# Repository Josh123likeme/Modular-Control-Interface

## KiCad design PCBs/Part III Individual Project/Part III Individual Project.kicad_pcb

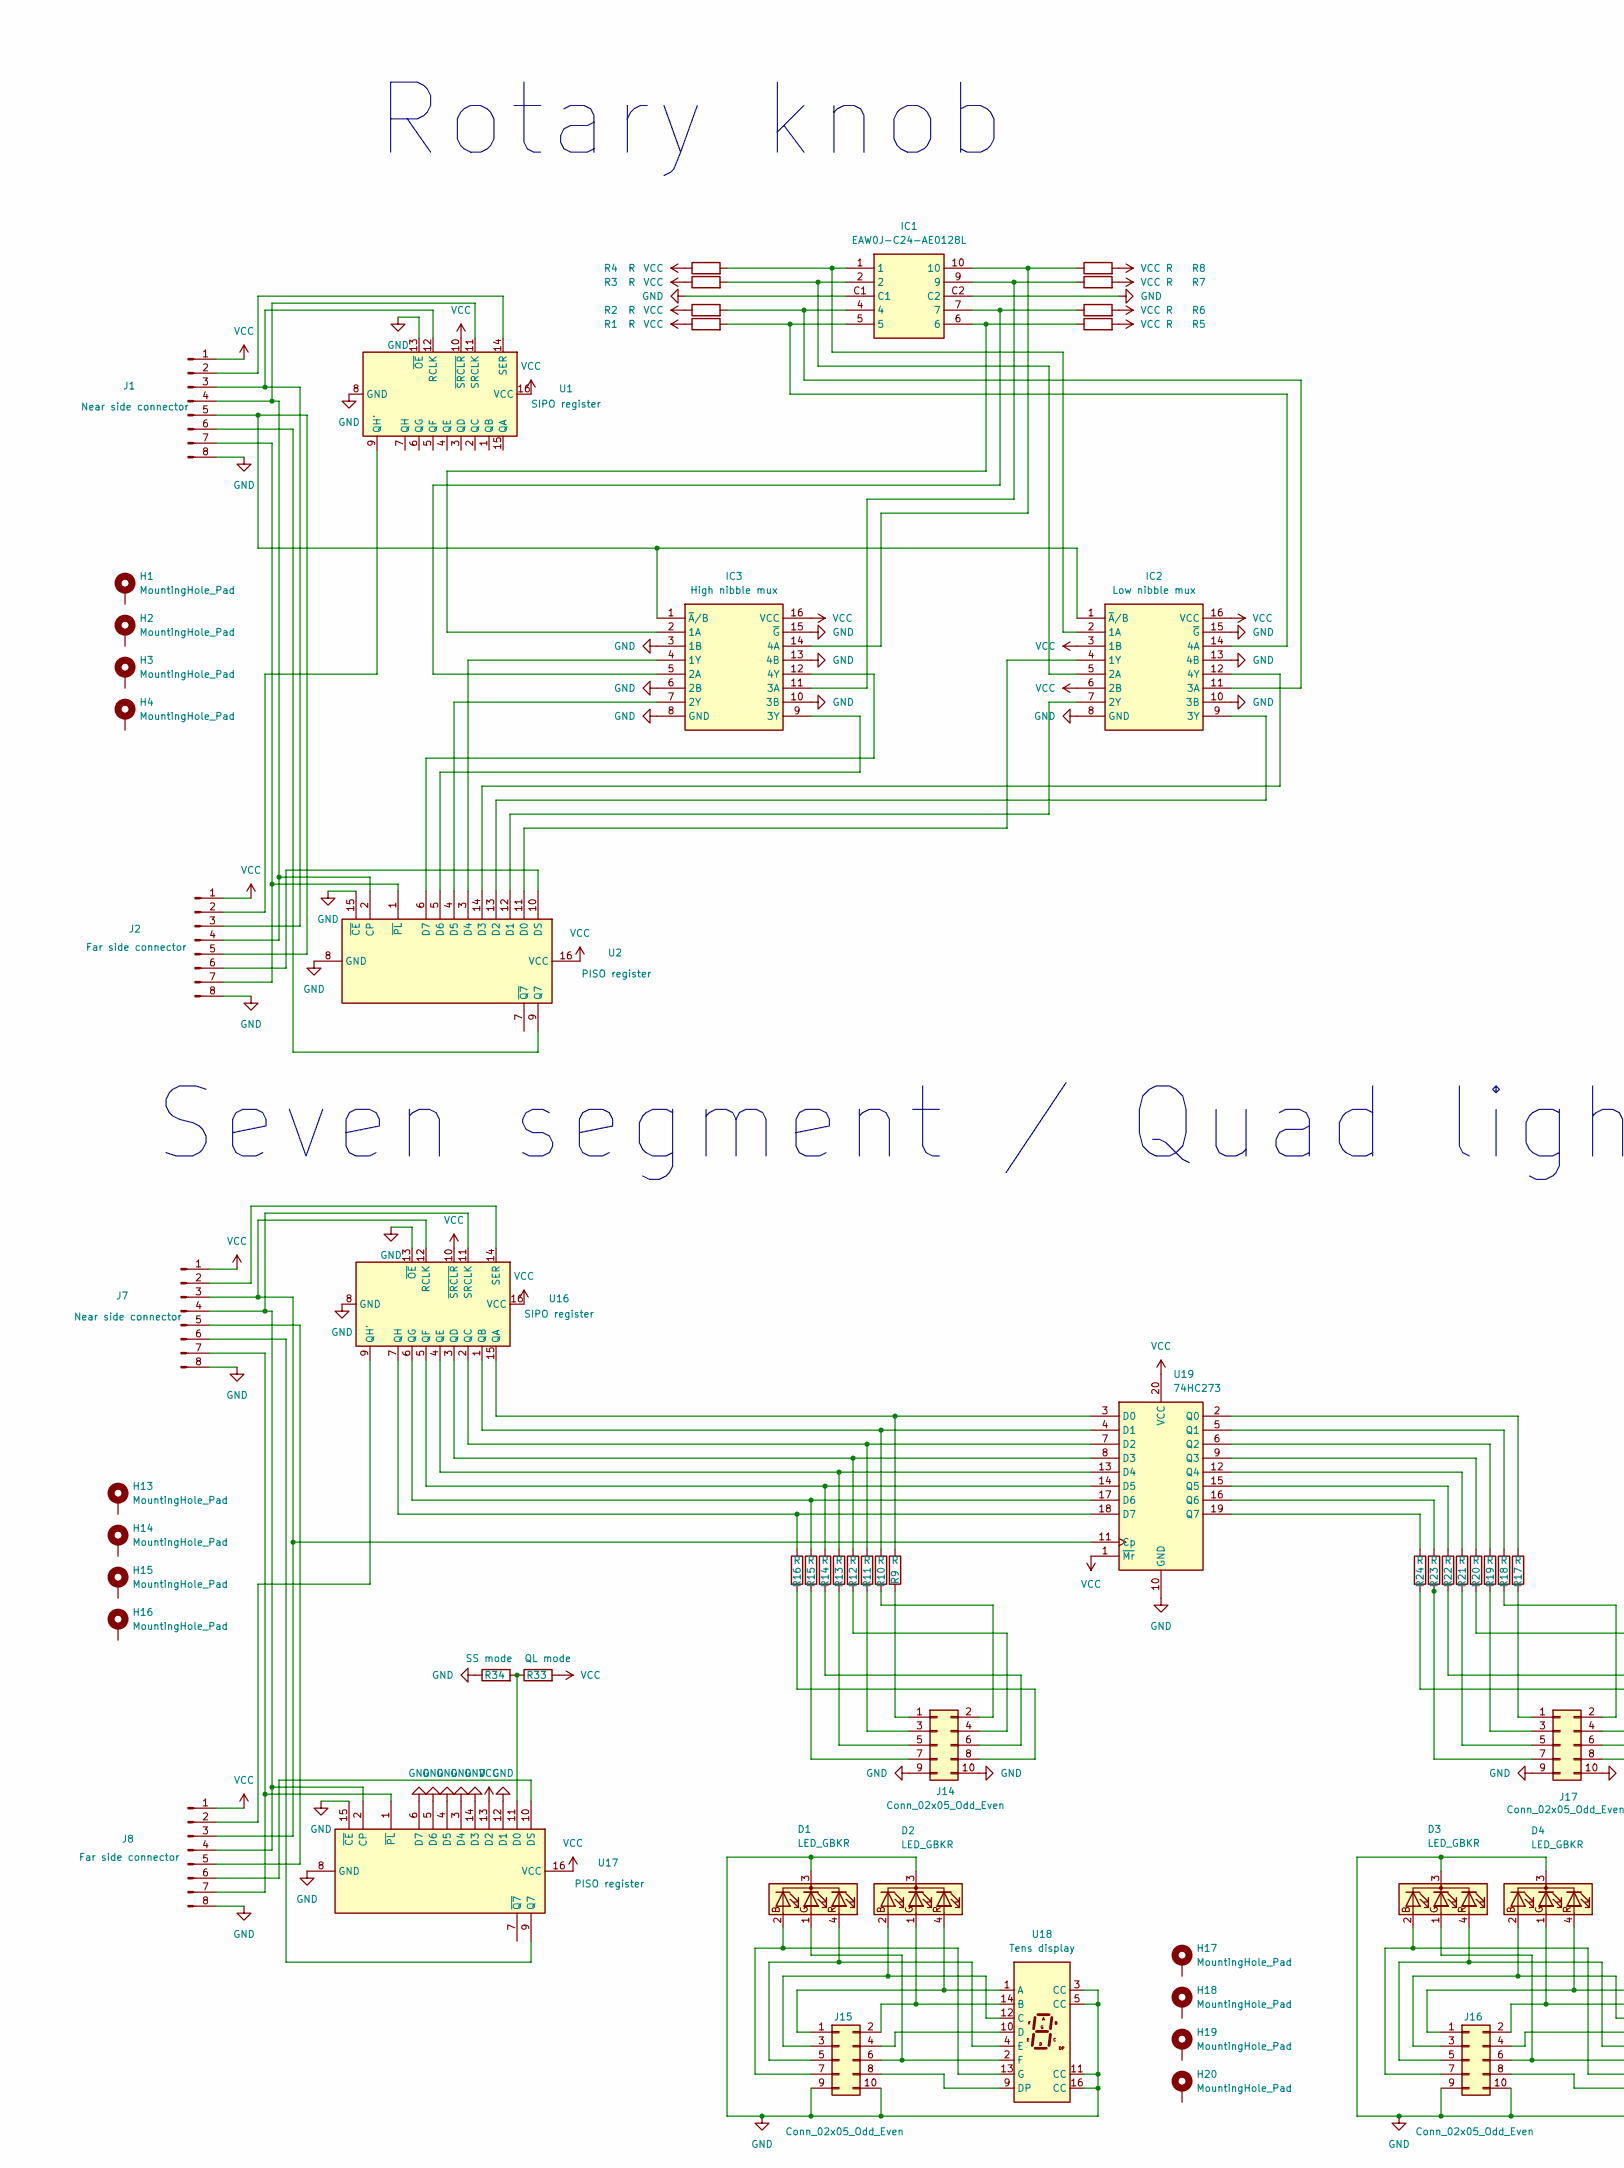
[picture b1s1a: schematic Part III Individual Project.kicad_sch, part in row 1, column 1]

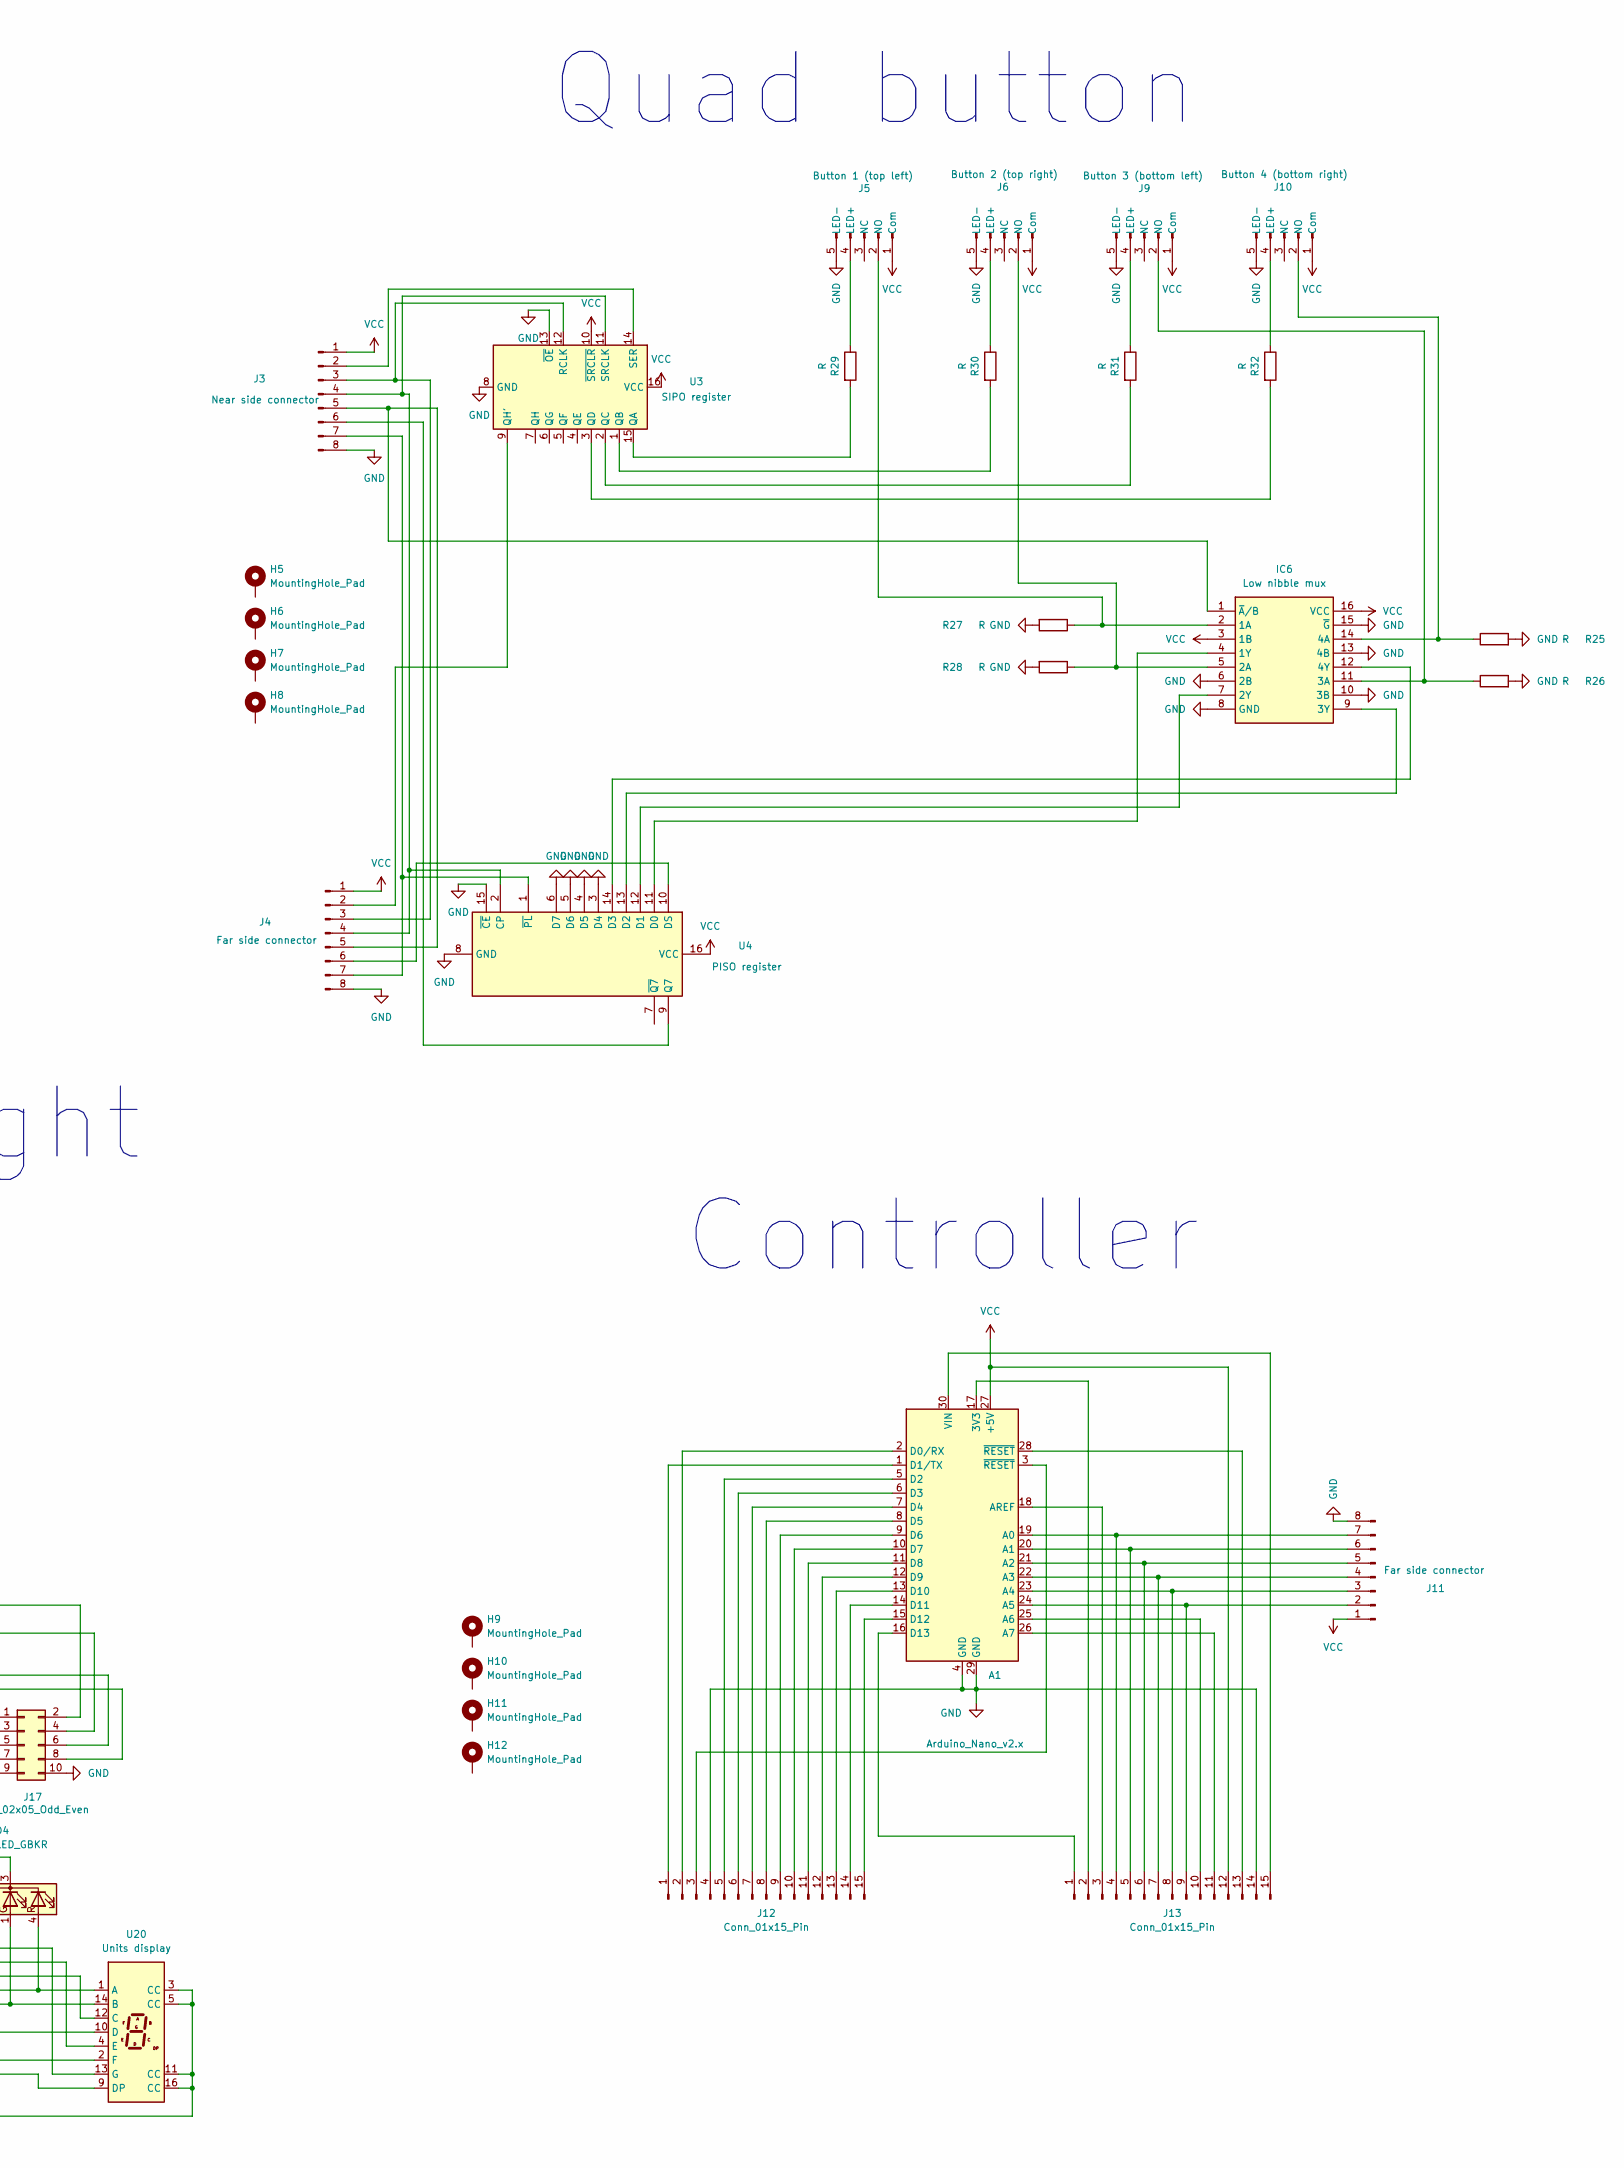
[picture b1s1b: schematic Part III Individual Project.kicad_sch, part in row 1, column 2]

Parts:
A1: Arduino_Nano_v2.x; Arduino Nano ATMEGA328P Headers Face Down
D1, D2, D3, D4: LED_GBKR; LED_D5.0mm-4_RGB_Wide_Pins
H1, H2, H3, H4, H5, H6, H7, H8, H9, H10, H11, H12, H13, H14, H15, H16, H17, H18, H19, H20: MountingHole_Pad; MountingHole_3.2mm_M3_Pad_Via
IC1: EAW0J-C24-AE0128L; EAW0JC24AE0128L; Mouser Part Number 652-EAW0J-C24-AEL
IC2, IC6: Low nibble mux; SOIC-16_3.9x9.9mm_P1.27mm; Mouser Part Number 595-SN74HC157DBR
IC3: High nibble mux; SOIC-16_3.9x9.9mm_P1.27mm; Mouser Part Number 595-SN74HC157DBR
J1, J3, J7: Near side connector; 8-way connector Pitch 2.54mm Lead Width 0.7mm
J2, J4, J8, J11: Far side connector; 8-way connector Pitch 2.54mm Lead Width 0.7mm
J5: Button 1 (top left); 16mm push button 5 pin 1NO 1NC
J6: Button 2 (top right); 16mm push button 5 pin 1NO 1NC
J9: Button 3 (bottom left); 16mm push button 5 pin 1NO 1NC
J10: Button 4 (bottom right); 16mm push button 5 pin 1NO 1NC
J12, J13: Conn_01x15_Pin; PinHeader_1x15_P2.54mm_Vertical
J14, J15, J16, J17: Conn_02x05_Odd_Even; PinHeader_2x05_P2.54mm_Vertical
R1, R2, R3, R4, R5, R6, R7, R8, R9, R10, R11, R12, R13, R14, R15, R16, R17, R18, R19, R20, R21, R22, R23, R24, R25, R26, R27, R28, R29, R30, R31, R32: R; R_0805_2012Metric_Pad1.20x1.40mm_HandSolder
R33: QL mode; R_0805_2012Metric_Pad1.20x1.40mm_HandSolder
R34: SS mode; R_0805_2012Metric_Pad1.20x1.40mm_HandSolder
U1, U3, U16: SIPO register; SOIC-16_3.9x9.9mm_P1.27mm
U2, U4, U17: PISO register; SOIC-16_3.9x9.9mm_P1.27mm
U18: Tens display; SC08-11GWA headers
U19: 74HC273; SOIC-20W_7.5x12.8mm_P1.27mm
U20: Units display; SC08-11GWA headers

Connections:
GND: A1.4 (GND), A1.29 (GND), D1.3 (K), D2.3 (K), D3.3 (K), D4.3 (K), IC1.C1, IC1.C2, IC2.8 (GND), IC2.10 (3B), IC2.13 (4B), IC2.15 (~G), IC3.3 (1B), IC3.6 (2B), IC3.8 (GND), IC3.10 (3B), IC3.13 (4B), IC3.15 (~G), IC6.6 (2B), IC6.8 (GND), IC6.10 (3B), IC6.13 (4B), IC6.15 (~G), J1.8, J2.8, J3.8, J4.8, J5.5 (LED-), J6.5 (LED-), J7.8, J8.8, J9.5 (LED-), J10.5 (LED-), J11.8, J12.4, J13.14, J14.9, J14.10, J15.9, J15.10, J16.9, J16.10, J17.9, J17.10, R25.2, R26.2, R27.2, R28.2, R34.1, U1.8 (GND), U1.13 (~OE), U2.8 (GND), U2.15 (~CE), U3.8 (GND), U3.13 (~OE), U4.3 (D4), U4.4 (D5), U4.5 (D6), U4.6 (D7), U4.8 (GND), U4.15 (~CE), U16.8 (GND), U16.13 (~OE), U17.3 (D4), U17.4 (D5), U17.5 (D6), U17.6 (D7), U17.8 (GND), U17.12 (D1), U17.14 (D3), U17.15 (~CE), U18.3 (CC), U18.5 (CC), U18.11 (CC), U18.16 (CC), U19.10 (GND), U20.3 (CC), U20.5 (CC), U20.11 (CC), U20.16 (CC)
unnamed: A1.17 (3V3), J13.2
unnamed: A1.19 (A0), J11.7, J13.4
unnamed: A1.20 (A1), J11.6, J13.5
unnamed: A1.21 (A2), J11.5, J13.6
unnamed: A1.22 (A3), J11.4, J13.7
unnamed: A1.23 (A4), J11.3, J13.8
unnamed: A1.24 (A5), J11.2, J13.9
unnamed: A1.25 (A6), J13.10
unnamed: A1.26 (A7), J13.11
unnamed: A1.18 (AREF), J13.3
unnamed: A1.2 (D0/RX), J12.2
unnamed: A1.1 (D1/TX), J12.1
unnamed: A1.5 (D2), J12.5
unnamed: A1.6 (D3), J12.6
unnamed: A1.7 (D4), J12.7
unnamed: A1.8 (D5), J12.8
unnamed: A1.9 (D6), J12.9
unnamed: A1.10 (D7), J12.10
unnamed: A1.11 (D8), J12.11
unnamed: A1.12 (D9), J12.12
unnamed: A1.13 (D10), J12.13
unnamed: A1.14 (D11), J12.14
unnamed: A1.15 (D12), J12.15
unnamed: A1.16 (D13), J13.1
unnamed: A1.30 (VIN), J13.15
unnamed: D1.2 (BA), J15.7, U18.13 (G)
unnamed: D1.1 (GA), J15.6, U18.2 (F)
unnamed: D1.4 (RA), J15.5, U18.4 (E)
unnamed: D2.2 (BA), J15.3, U18.12 (C)
unnamed: D2.1 (GA), J15.2, U18.14 (B)
unnamed: D2.4 (RA), J15.1, U18.1 (A)
unnamed: D3.2 (BA), J16.7, U20.13 (G)
unnamed: D3.1 (GA), J16.6, U20.2 (F)
unnamed: D3.4 (RA), J16.5, U20.4 (E)
unnamed: D4.2 (BA), J16.3, U20.12 (C)
unnamed: D4.1 (GA), J16.2, U20.14 (B)
unnamed: D4.4 (RA), J16.1, U20.1 (A)
unnamed: IC1.1, IC2.2 (1A), R4.2
unnamed: IC2.4 (1Y), U2.11 (D0)
unnamed: IC1.2, IC2.5 (2A), R3.2
unnamed: IC2.7 (2Y), U2.12 (D1)
unnamed: IC1.4, IC2.11 (3A), R2.2
unnamed: IC2.9 (3Y), U2.13 (D2)
unnamed: IC1.5, IC2.14 (4A), R1.2
unnamed: IC2.12 (4Y), U2.14 (D3)
unnamed: IC2.1 (~A/B), IC3.1 (~A/B), J1.5, J2.5
unnamed: IC1.6, IC3.2 (1A), R5.1
unnamed: IC3.4 (1Y), U2.3 (D4)
unnamed: IC1.7, IC3.5 (2A), R6.1
unnamed: IC3.7 (2Y), U2.4 (D5)
unnamed: IC1.9, IC3.11 (3A), R7.1
unnamed: IC3.9 (3Y), U2.5 (D6)
unnamed: IC1.10, IC3.14 (4A), R8.1
unnamed: IC3.12 (4Y), U2.6 (D7)
unnamed: IC6.2 (1A), J5.2 (NO), R27.1
unnamed: IC6.4 (1Y), U4.11 (D0)
unnamed: IC6.5 (2A), J6.2 (NO), R28.1
unnamed: IC6.7 (2Y), U4.12 (D1)
unnamed: IC6.11 (3A), J9.2 (NO), R26.1
unnamed: IC6.9 (3Y), U4.13 (D2)
unnamed: IC6.14 (4A), J10.2 (NO), R25.1
unnamed: IC6.12 (4Y), U4.14 (D3)
unnamed: IC6.1 (~A/B), J3.5, J4.5
unnamed: J1.2, U1.14 (SER)
unnamed: J1.3, J2.3, U1.12 (RCLK)
unnamed: J1.4, J2.4, U1.11 (SRCLK), U2.2 (CP)
unnamed: J1.6, U2.9 (Q7)
unnamed: J1.7, J2.7, U2.1 (~PL)
unnamed: J2.2, U1.9 (QH')
unnamed: J2.6, U2.10 (DS)
unnamed: J3.2, U3.14 (SER)
unnamed: J3.3, J4.3, U3.12 (RCLK)
unnamed: J3.4, J4.4, U3.11 (SRCLK), U4.2 (CP)
unnamed: J3.6, U4.9 (Q7)
unnamed: J3.7, J4.7, U4.1 (~PL)
unnamed: J4.2, U3.9 (QH')
unnamed: J4.6, U4.10 (DS)
unnamed: J5.4 (LED+), R29.1
unnamed: J6.4 (LED+), R30.1
unnamed: J7.2, U16.14 (SER)
unnamed: J7.3, J8.3, U16.12 (RCLK), U19.11 (Cp)
unnamed: J7.4, J8.4, U16.11 (SRCLK), U17.2 (CP)
unnamed: J7.5, J8.5
unnamed: J7.6, U17.9 (Q7)
unnamed: J7.7, J8.7, U17.1 (~PL)
unnamed: J8.2, U16.9 (QH')
unnamed: J8.6, U17.10 (DS)
unnamed: J9.4 (LED+), R31.1
unnamed: J10.4 (LED+), R32.1
unnamed: A1.3 (~RESET), J12.3
unnamed: A1.28 (~RESET), J13.13
unnamed: J14.1, R9.2
unnamed: J14.2, R10.2
unnamed: J14.3, R11.2
unnamed: J14.4, R12.2
unnamed: J14.5, R13.2
unnamed: J14.6, R14.2
unnamed: J14.7, R15.2
unnamed: J14.8, R16.2
unnamed: J15.4, U18.10 (D)
unnamed: J15.8, U18.9 (DP)
unnamed: J16.4, U20.10 (D)
unnamed: J16.8, U20.9 (DP)
unnamed: J17.1, R17.2
unnamed: J17.2, R18.2
unnamed: J17.3, R19.2
unnamed: J17.4, R20.2
unnamed: J17.5, R21.2
unnamed: J17.6, R22.2
unnamed: J17.7, R23.2
unnamed: J17.8, R24.2
unnamed: R29.2, U3.15 (QA)
unnamed: R30.2, U3.1 (QB)
unnamed: R31.2, U3.2 (QC)
unnamed: R32.2, U3.3 (QD)
unnamed: R9.1, U16.15 (QA), U19.3 (D0)
unnamed: R10.1, U16.1 (QB), U19.4 (D1)
unnamed: R11.1, U16.2 (QC), U19.7 (D2)
unnamed: R12.1, U16.3 (QD), U19.8 (D3)
unnamed: R13.1, U16.4 (QE), U19.13 (D4)
unnamed: R14.1, U16.5 (QF), U19.14 (D5)
unnamed: R15.1, U16.6 (QG), U19.17 (D6)
unnamed: R16.1, U16.7 (QH), U19.18 (D7)
unnamed: R33.1, R34.2, U17.11 (D0)
unnamed: R17.1, U19.2 (Q0)
unnamed: R18.1, U19.5 (Q1)
unnamed: R19.1, U19.6 (Q2)
unnamed: R20.1, U19.9 (Q3)
unnamed: R21.1, U19.12 (Q4)
unnamed: R22.1, U19.15 (Q5)
unnamed: R23.1, U19.16 (Q6)
unnamed: R24.1, U19.19 (Q7)
VCC: A1.27 (+5V), IC2.3 (1B), IC2.6 (2B), IC2.16 (VCC), IC3.16 (VCC), IC6.3 (1B), IC6.16 (VCC), J1.1, J2.1, J3.1, J4.1, J5.1 (Com), J6.1 (Com), J7.1, J8.1, J9.1 (Com), J10.1 (Com), J11.1, J13.12, R1.1, R2.1, R3.1, R4.1, R5.2, R6.2, R7.2, R8.2, R33.2, U1.10 (~SRCLR), U1.16 (VCC), U2.16 (VCC), U3.10 (~SRCLR), U3.16 (VCC), U4.16 (VCC), U16.10 (~SRCLR), U16.16 (VCC), U17.13 (D2), U17.16 (VCC), U19.1 (~Mr), U19.20 (VCC)

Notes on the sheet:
Seven segment / Quad light
Controller
Rotary knob
Quad button

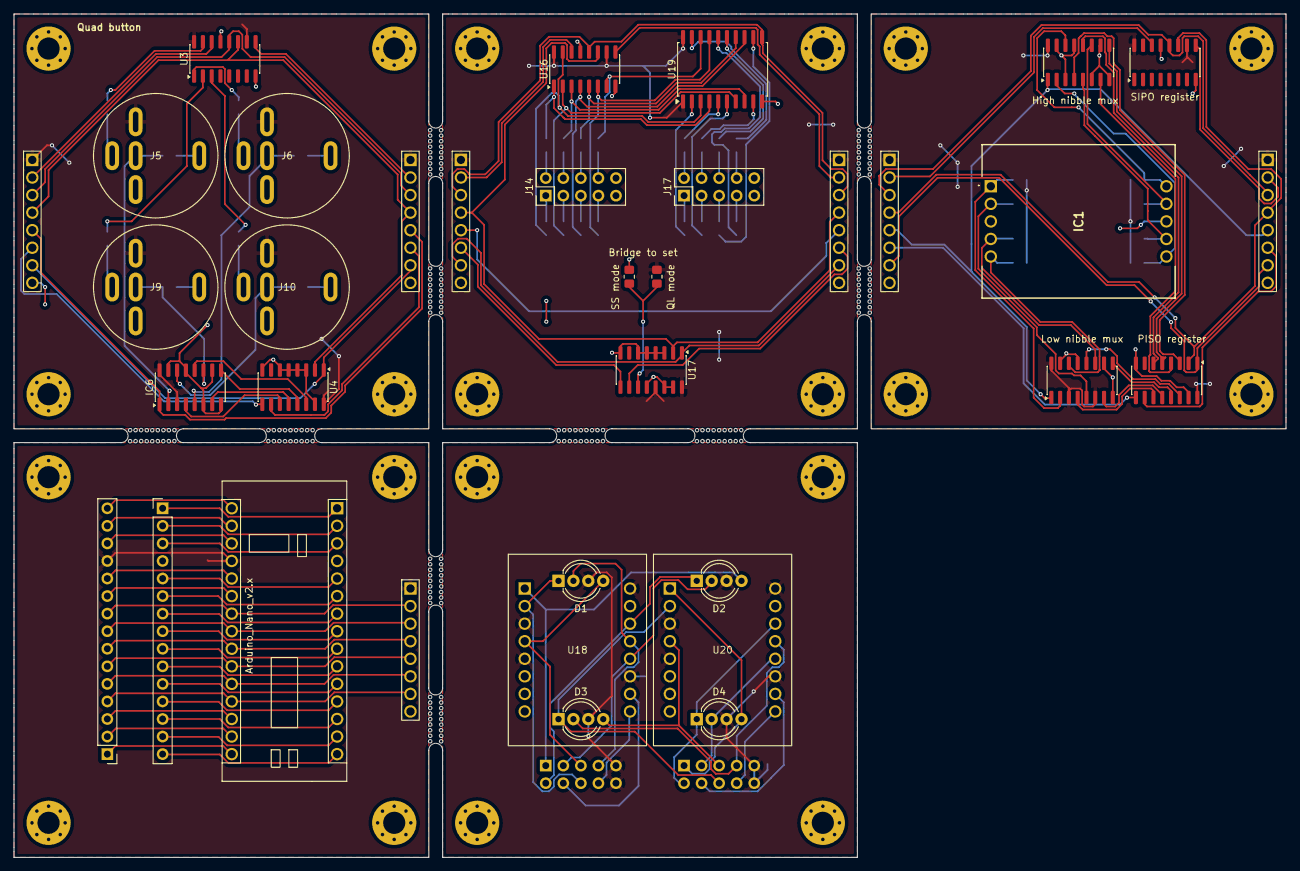
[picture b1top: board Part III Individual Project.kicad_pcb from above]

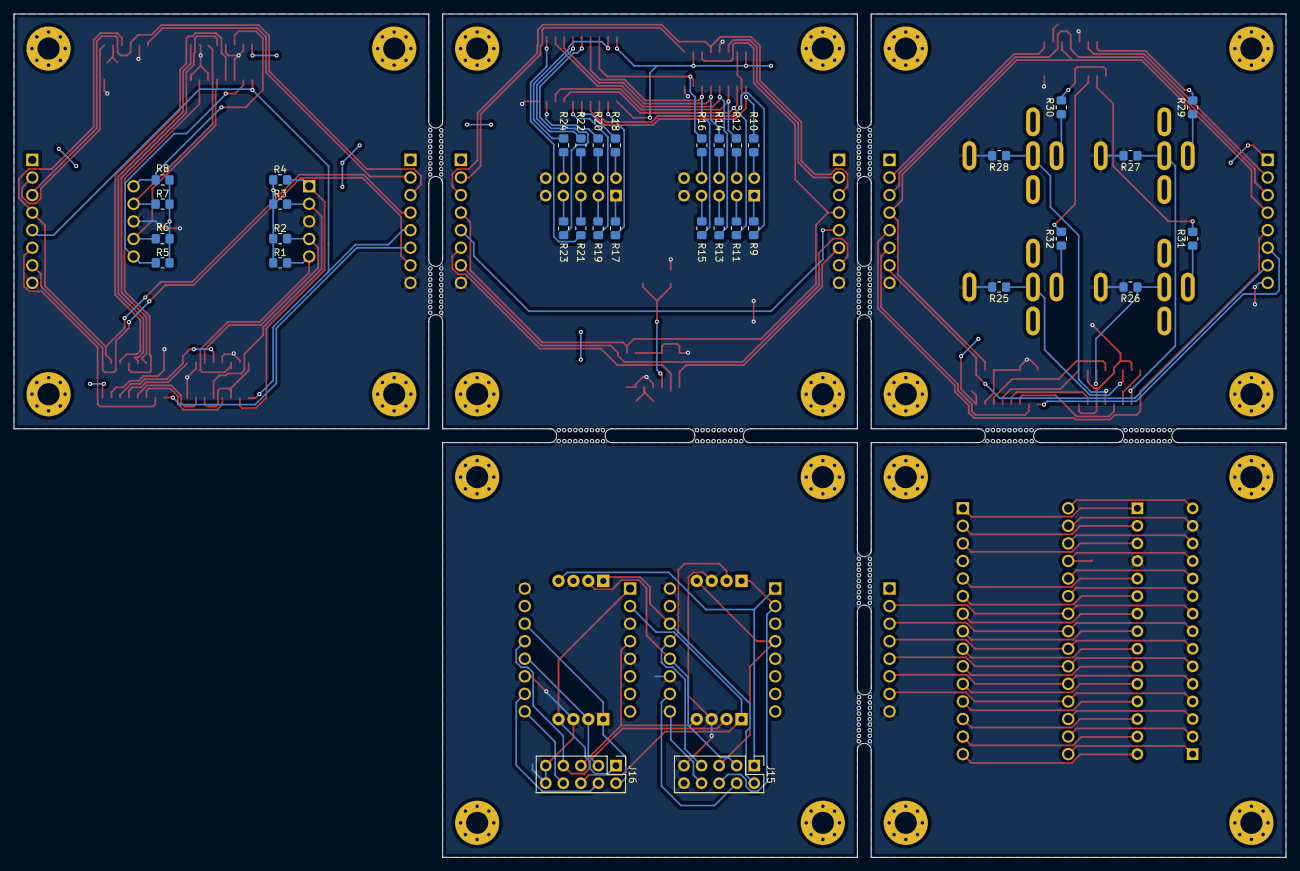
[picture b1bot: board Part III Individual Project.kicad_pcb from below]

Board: 2 copper layers, 184.0 x 122.0 mm, 99 parts (34 on the bottom side), 134 nets.

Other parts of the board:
mouse-bite-2mm-4mm, mouse-bite-2mm-4mm#2, mouse-bite-2mm-4mm#3, mouse-bite-2mm-4mm#4, mouse-bite-2mm-4mm#5, mouse-bite-2mm-4mm#6, mouse-bite-2mm-4mm#7, mouse-bite-2mm-4mm#8, mouse-bite-2mm-4mm#9, mouse-bite-2mm-4mm#10: VAL**; mouse_bite_2mm_7mm
